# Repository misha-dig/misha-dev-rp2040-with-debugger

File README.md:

# misha-dev-rp2040-with-debugger
A compact-sized development board with two switchable debugger modes (BOOTSEL and SWD (debug/flash)) powered by a type-C receptacle connector.

# Description project
Single board with dual methods of uploading firmware into MCU RP2040 and not longer need to use Raspberry Pi debug probe, if use this board. 

# Requirement
Install and configure Raspberry Pi debug probe code, you can download from links https://github.com/raspberrypi/debugprobe
Will provided only board_pico_config.h in software directory. You will need to replace file from orginal file.

To install required lastest version of Raspberry Pi Pico SDK. Recommended version PICO SDK is above 2.0.0

# Testing SWD flashing and UART

Will provide binaries and instruction later.

# Technical specification
- Two RP2040 MCU (one for main functions of development board and one for debugger)
- USB Type-C connector receptacle (Best solution that not require to find uncommon USB cables)
- Normal input voltage from USB is 5.0 V, but absolute range is (4.5 - 5.5 VDC). This development board can power only USB cable as first prototyping. Unfortunately, don't allow to use external power source even 5V in current time. Use it is risk to damage your board. 
- Maximum output recommend current is 250mA for 3.3 voltage regulation, but 500mA is absolute maximum current in both output voltage 3.3V and 5.0V to avoid excessing heating voltage regulator due solder paste has melting point 138 C. 
- MCU clock 133 MHz
- RAM 264 kB.
- Flash memory size 16 - 128 Mbit, depending in your prototyping. Use Winbond flash memory series W25QxxxJVxxx as Raspberry Pi recommendation for RP2040 MCU. Required external flash memory each RP2040 in both MCUs. 

# Credit
* [Debugprobe](https://github.com/raspberrypi/debugprobe) (but I take portion source of code for only configuration of debugprobe due licensing complex and restriction of modification). I will planed to replace CMSIS-DAP software and hardware that support full open-source license and save BOM cost. Configuration CMSIS-DAP is licensed MIT, e.g. [board_pico_config.h](https://github.com/raspberrypi/debugprobe/blob/master/include/board_pico_config.h)

* [Raspberry Pi Documentation](https://www.raspberrypi.com/documentation/microcontrollers/) (Included: Hardware design with RP2040 and Getting started with RP2040)

* [Raspberry Pi Pico Datasheet](https://datasheets.raspberrypi.com/pico/pico-datasheet.pdf)

* [Getting started with Raspberry Pi
Pico-series](https://datasheets.raspberrypi.com/pico/getting-started-with-pico.pdf)

* [Raspberry Pi Licence Information](https://datasheets.raspberrypi.com/licence.html)

* [Licensing](https://www.raspberrypi.com/licensing/)

* [The design is based rp2040/Minimal-KiCAD.zip](https://datasheets.raspberrypi.com/rp2040/Minimal-KiCAD.zip) (Use downloaded circuits with mapping debugging and serial ports between two RP2040 MCUs)

* Thanks for developing excellent RP2040 MCU to Raspberry Pi that can develop software and hardware opensource!

# What I want to ask  

* Good luck with building your development board with debugger.
* I happy that help to solve problems

# Disclaimer and license

* PCB and sechmatics design are licensed licensed under CC BY-NC-ND 4.0. (C) Misha Zaslavskis

DESIGNS ARE PROVIDED “AS IS” AND THE AUTHOR DISCLAIMS ALL WARRANTIES WITH REGARD TO THESE DESIGNS INCLUDING ALL IMPLIED WARRANTIES OF MERCHANTABILITY AND FITNESS. IN NO EVENT SHALL THE AUTHOR BE LIABLE FOR ANY SPECIAL, DIRECT, INDIRECT, OR CONSEQUENTIAL DAMAGES OR ANY DAMAGES WHATSOEVER RESULTING FROM LOSS OF USE, DATA OR PROFITS, WHETHER IN AN ACTION OF CONTRACT, NEGLIGENCE OR OTHER TORTIOUS ACTION, ARISING OUT OF OR IN CONNECTION WITH THE USE OR PERFORMANCE OF THESE DESIGNS.

* Software (configuration of debugprobe) are licensed under MIT. (C) 2023 Raspberry Pi (Trading) Ltd.

THE SOFTWARE IS PROVIDED “AS IS”, WITHOUT WARRANTY OF ANY KIND, EXPRESS OR IMPLIED, INCLUDING BUT NOT LIMITED TO THE WARRANTIES OF MERCHANTABILITY, FITNESS FOR A PARTICULAR PURPOSE AND NONINFRINGEMENT. IN NO EVENT SHALL THE AUTHORS OR COPYRIGHT HOLDERS BE LIABLE FOR ANY CLAIM, DAMAGES OR OTHER LIABILITY, WHETHER IN AN ACTION OF CONTRACT, TORT OR OTHERWISE, ARISING FROM, OUT OF OR IN CONNECTION WITH THE SOFTWARE OR THE USE OR OTHER DEALINGS IN THE SOFTWARE.

* Software (testing API for this board) are licensed under BSD 3-Clause License. (C) Misha Zaslavskis

THIS SOFTWARE IS PROVIDED BY THE COPYRIGHT HOLDERS AND CONTRIBUTORS "AS IS"
AND ANY EXPRESS OR IMPLIED WARRANTIES, INCLUDING, BUT NOT LIMITED TO, THE
IMPLIED WARRANTIES OF MERCHANTABILITY AND FITNESS FOR A PARTICULAR PURPOSE ARE
DISCLAIMED. IN NO EVENT SHALL THE COPYRIGHT HOLDER OR CONTRIBUTORS BE LIABLE
FOR ANY DIRECT, INDIRECT, INCIDENTAL, SPECIAL, EXEMPLARY, OR CONSEQUENTIAL
DAMAGES (INCLUDING, BUT NOT LIMITED TO, PROCUREMENT OF SUBSTITUTE GOODS OR
SERVICES; LOSS OF USE, DATA, OR PROFITS; OR BUSINESS INTERRUPTION) HOWEVER
CAUSED AND ON ANY THEORY OF LIABILITY, WHETHER IN CONTRACT, STRICT LIABILITY,
OR TORT (INCLUDING NEGLIGENCE OR OTHERWISE) ARISING IN ANY WAY OUT OF THE USE
OF THIS SOFTWARE, EVEN IF ADVISED OF THE POSSIBILITY OF SUCH DAMAGE.

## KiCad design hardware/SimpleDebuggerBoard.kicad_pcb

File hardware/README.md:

## KiCAD Project Folder
This forder is contain KiCAD project files, so you can view/edit PCB and sechmatics by downloading this folder if neccesary.

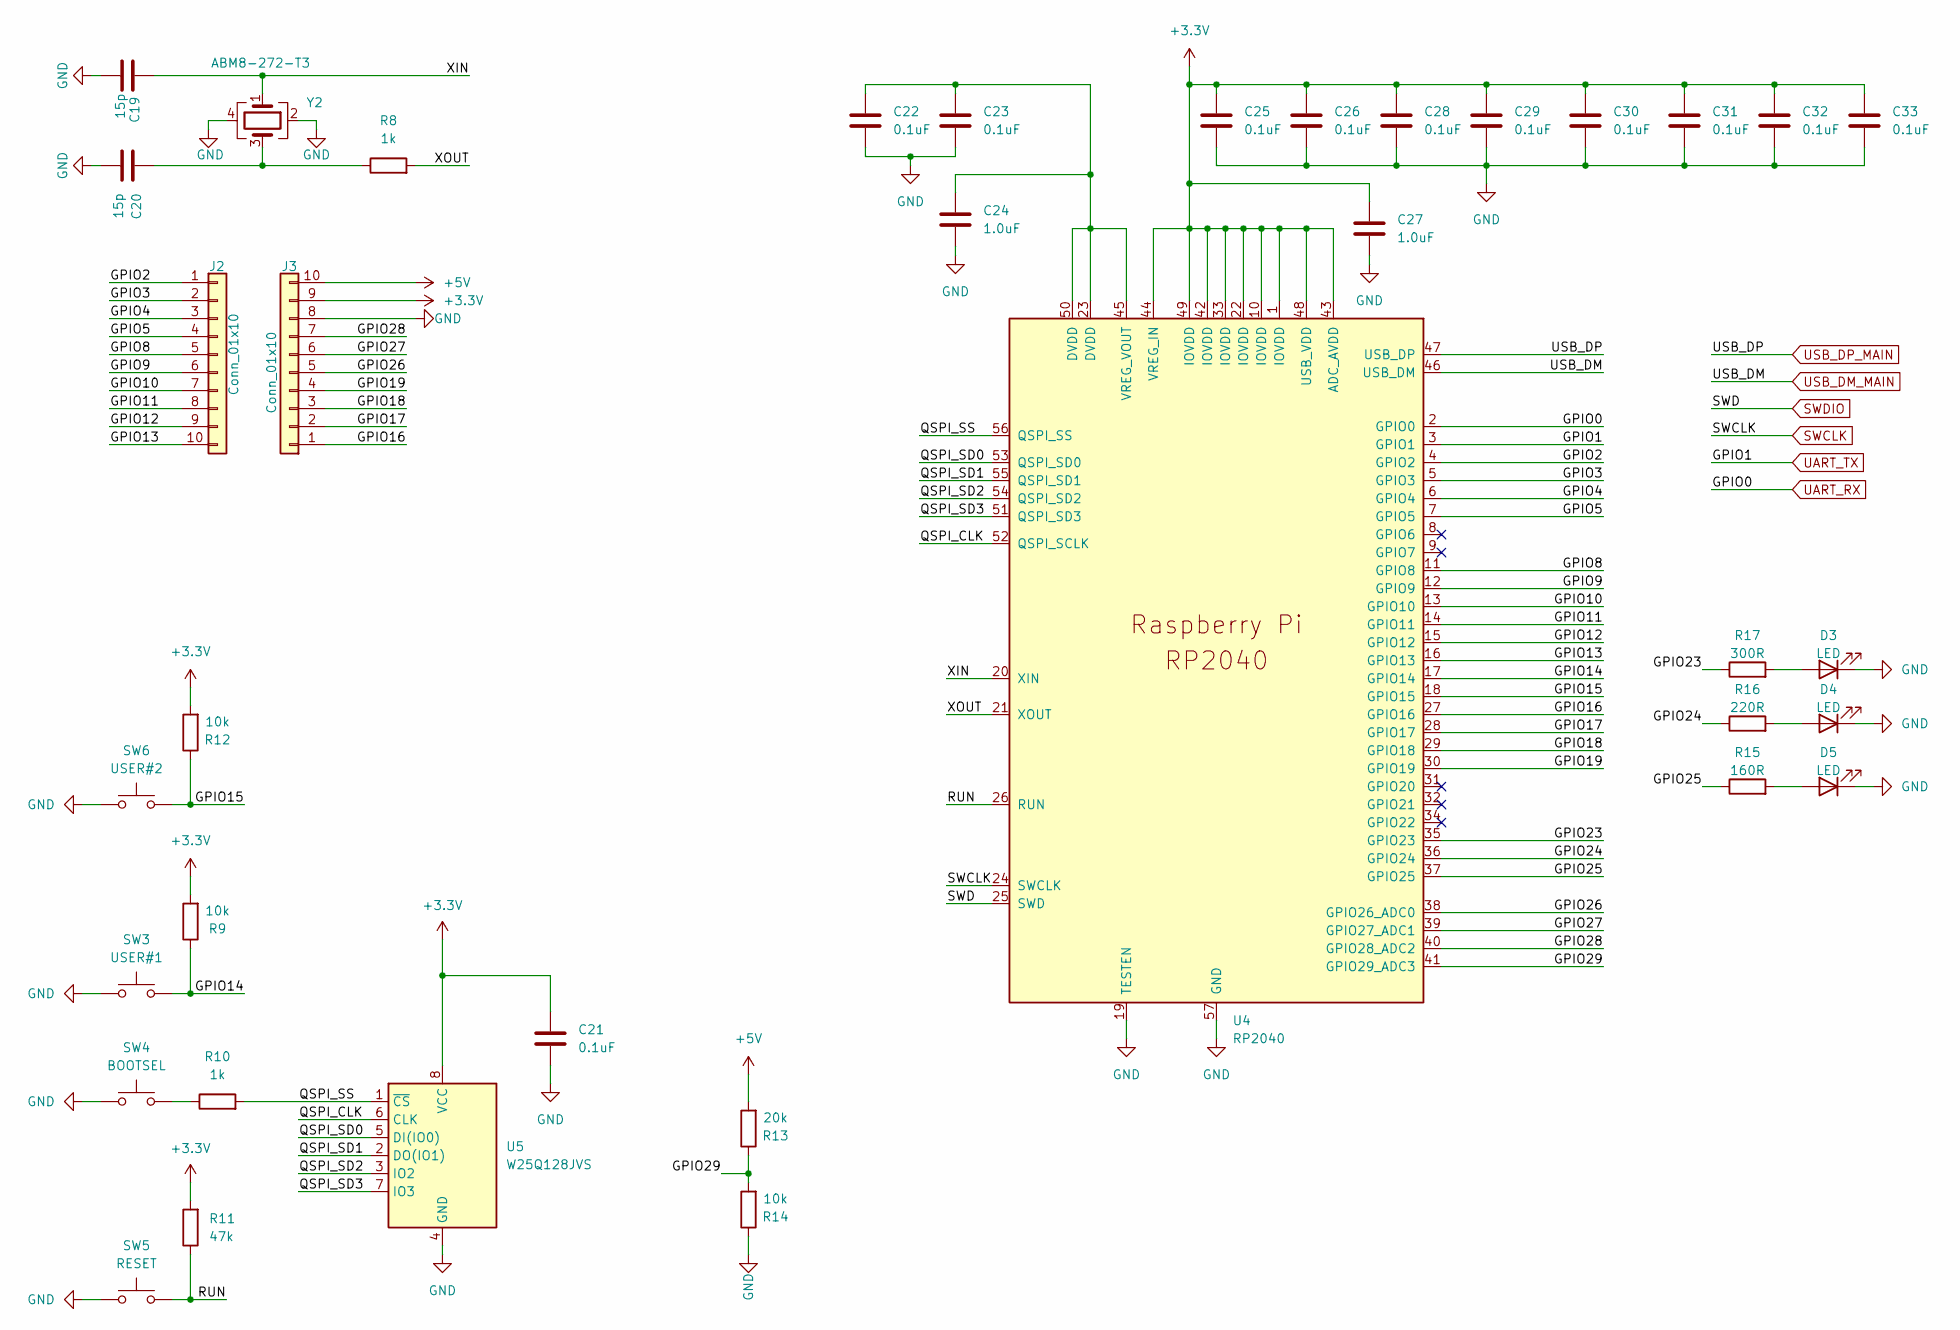
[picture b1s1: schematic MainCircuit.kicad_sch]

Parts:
C19, C20: 15p; C_0402_1005Metric_Pad0.74x0.62mm_HandSolder
C21, C22, C23, C25, C26, C28, C29, C30, C31, C32, C33: 0.1uF; C_0402_1005Metric_Pad0.74x0.62mm_HandSolder
C24, C27: 1.0uF; C_0603_1608Metric_Pad1.08x0.95mm_HandSolder
D3, D4, D5: LED; LED_0603_1608Metric
J2, J3: Conn_01x10; PinHeader_1x10_P2.54mm_Vertical
R8, R10: 1k; R_0402_1005Metric_Pad0.72x0.64mm
R9, R12, R14: 10k; R_0402_1005Metric_Pad0.72x0.64mm
R11: 47k; R_0402_1005Metric_Pad0.72x0.64mm
R13: 20k; R_0402_1005Metric_Pad0.72x0.64mm
R15: 160R; R_0402_1005Metric_Pad0.72x0.64mm
R16: 220R; R_0402_1005Metric_Pad0.72x0.64mm
R17: 300R; R_0402_1005Metric_Pad0.72x0.64mm
SW3: USER#1; SW_SPST_PTS810
SW4: BOOTSEL; SW_SPST_PTS810
SW5: RESET; SW_SPST_PTS810
SW6: USER#2; SW_SPST_PTS810
U4: RP2040; RP2040-QFN-56
U5: W25Q128JVS; SOIC-8_5.23x5.23mm_P1.27mm
Y2: ABM8-272-T3; Crystal_SMD_3225-4Pin_3.2x2.5mm

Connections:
+3.3V: C21.1, C25.1, C26.1, C27.1, C28.1, C29.1, C30.1, C31.1, C32.1, C33.1, J3.9, R9.2, R11.2, R12.2, U4.1 (IOVDD), U4.10 (IOVDD), U4.22 (IOVDD), U4.33 (IOVDD), U4.42 (IOVDD), U4.43 (ADC_AVDD), U4.44 (VREG_IN), U4.48 (USB_VDD), U4.49 (IOVDD), U5.8 (VCC); also elsewhere on the board
+5V: J3.10, R13.2; also elsewhere on the board
/MainCircuit/GPIO2: J2.1, U4.4 (GPIO2)
/MainCircuit/GPIO3: J2.2, U4.5 (GPIO3)
/MainCircuit/GPIO4: J2.3, U4.6 (GPIO4)
/MainCircuit/GPIO5: J2.4, U4.7 (GPIO5)
/MainCircuit/GPIO8: J2.5, U4.11 (GPIO8)
/MainCircuit/GPIO9: J2.6, U4.12 (GPIO9)
/MainCircuit/GPIO10: J2.7, U4.13 (GPIO10)
/MainCircuit/GPIO11: J2.8, U4.14 (GPIO11)
/MainCircuit/GPIO12: J2.9, U4.15 (GPIO12)
/MainCircuit/GPIO13: J2.10, U4.16 (GPIO13)
/MainCircuit/GPIO14: R9.1, SW3.1, U4.17 (GPIO14)
/MainCircuit/GPIO15: R12.1, SW6.1, U4.18 (GPIO15)
/MainCircuit/GPIO16: J3.1, U4.27 (GPIO16)
/MainCircuit/GPIO17: J3.2, U4.28 (GPIO17)
/MainCircuit/GPIO18: J3.3, U4.29 (GPIO18)
/MainCircuit/GPIO19: J3.4, U4.30 (GPIO19)
/MainCircuit/GPIO23: R17.1, U4.35 (GPIO23)
/MainCircuit/GPIO24: R16.1, U4.36 (GPIO24)
/MainCircuit/GPIO25: R15.1, U4.37 (GPIO25)
/MainCircuit/GPIO26: J3.5, U4.38 (GPIO26_ADC0)
/MainCircuit/GPIO27: J3.6, U4.39 (GPIO27_ADC1)
/MainCircuit/GPIO28: J3.7, U4.40 (GPIO28_ADC2)
/MainCircuit/GPIO29: R13.1, R14.2, U4.41 (GPIO29_ADC3)
/MainCircuit/QSPI_CLK: U4.52 (QSPI_SCLK), U5.6 (CLK)
/MainCircuit/QSPI_SD0: U4.53 (QSPI_SD0), U5.5 (DI(IO0))
/MainCircuit/QSPI_SD1: U4.55 (QSPI_SD1), U5.2 (DO(IO1))
/MainCircuit/QSPI_SD2: U4.54 (QSPI_SD2), U5.3 (IO2)
/MainCircuit/QSPI_SD3: U4.51 (QSPI_SD3), U5.7 (IO3)
/MainCircuit/QSPI_SS: R10.2, U4.56 (QSPI_SS), U5.1 (~CS)
/MainCircuit/RUN: R11.1, SW5.2, U4.26 (RUN)
/MainCircuit/XIN: C19.2, U4.20 (XIN), Y2.1
/MainCircuit/XOUT: R8.2, U4.21 (XOUT)
GND: C19.1, C20.1, C21.2, C22.2, C23.2, C24.2, C25.2, C26.2, C27.2, C28.2, C29.2, C30.2, C31.2, C32.2, C33.2, D3.1 (K), D4.1 (K), D5.1 (K), J3.8, R14.1, SW3.2, SW4.1, SW5.1, SW6.2, U4.19 (TESTEN), U4.57 (GND), U5.4 (GND), Y2.2, Y2.4; also elsewhere on the board
unnamed: C20.2, R8.1, Y2.3
unnamed: D3.2 (A), R17.2
unnamed: D4.2 (A), R16.2
unnamed: D5.2 (A), R15.2
unnamed: R10.1, SW4.2
unnamed: C22.1, C23.1, C24.1, U4.23 (DVDD), U4.45 (VREG_VOUT), U4.50 (DVDD)
SWCLK: U4.24 (SWCLK); also elsewhere on the board
SWDIO: U4.25 (SWD); also elsewhere on the board
UART_RX: U4.2 (GPIO0); also elsewhere on the board
UART_TX: U4.3 (GPIO1); also elsewhere on the board
USB_DM_MAIN: U4.46 (USB_DM); also elsewhere on the board
USB_DP_MAIN: U4.47 (USB_DP); also elsewhere on the board

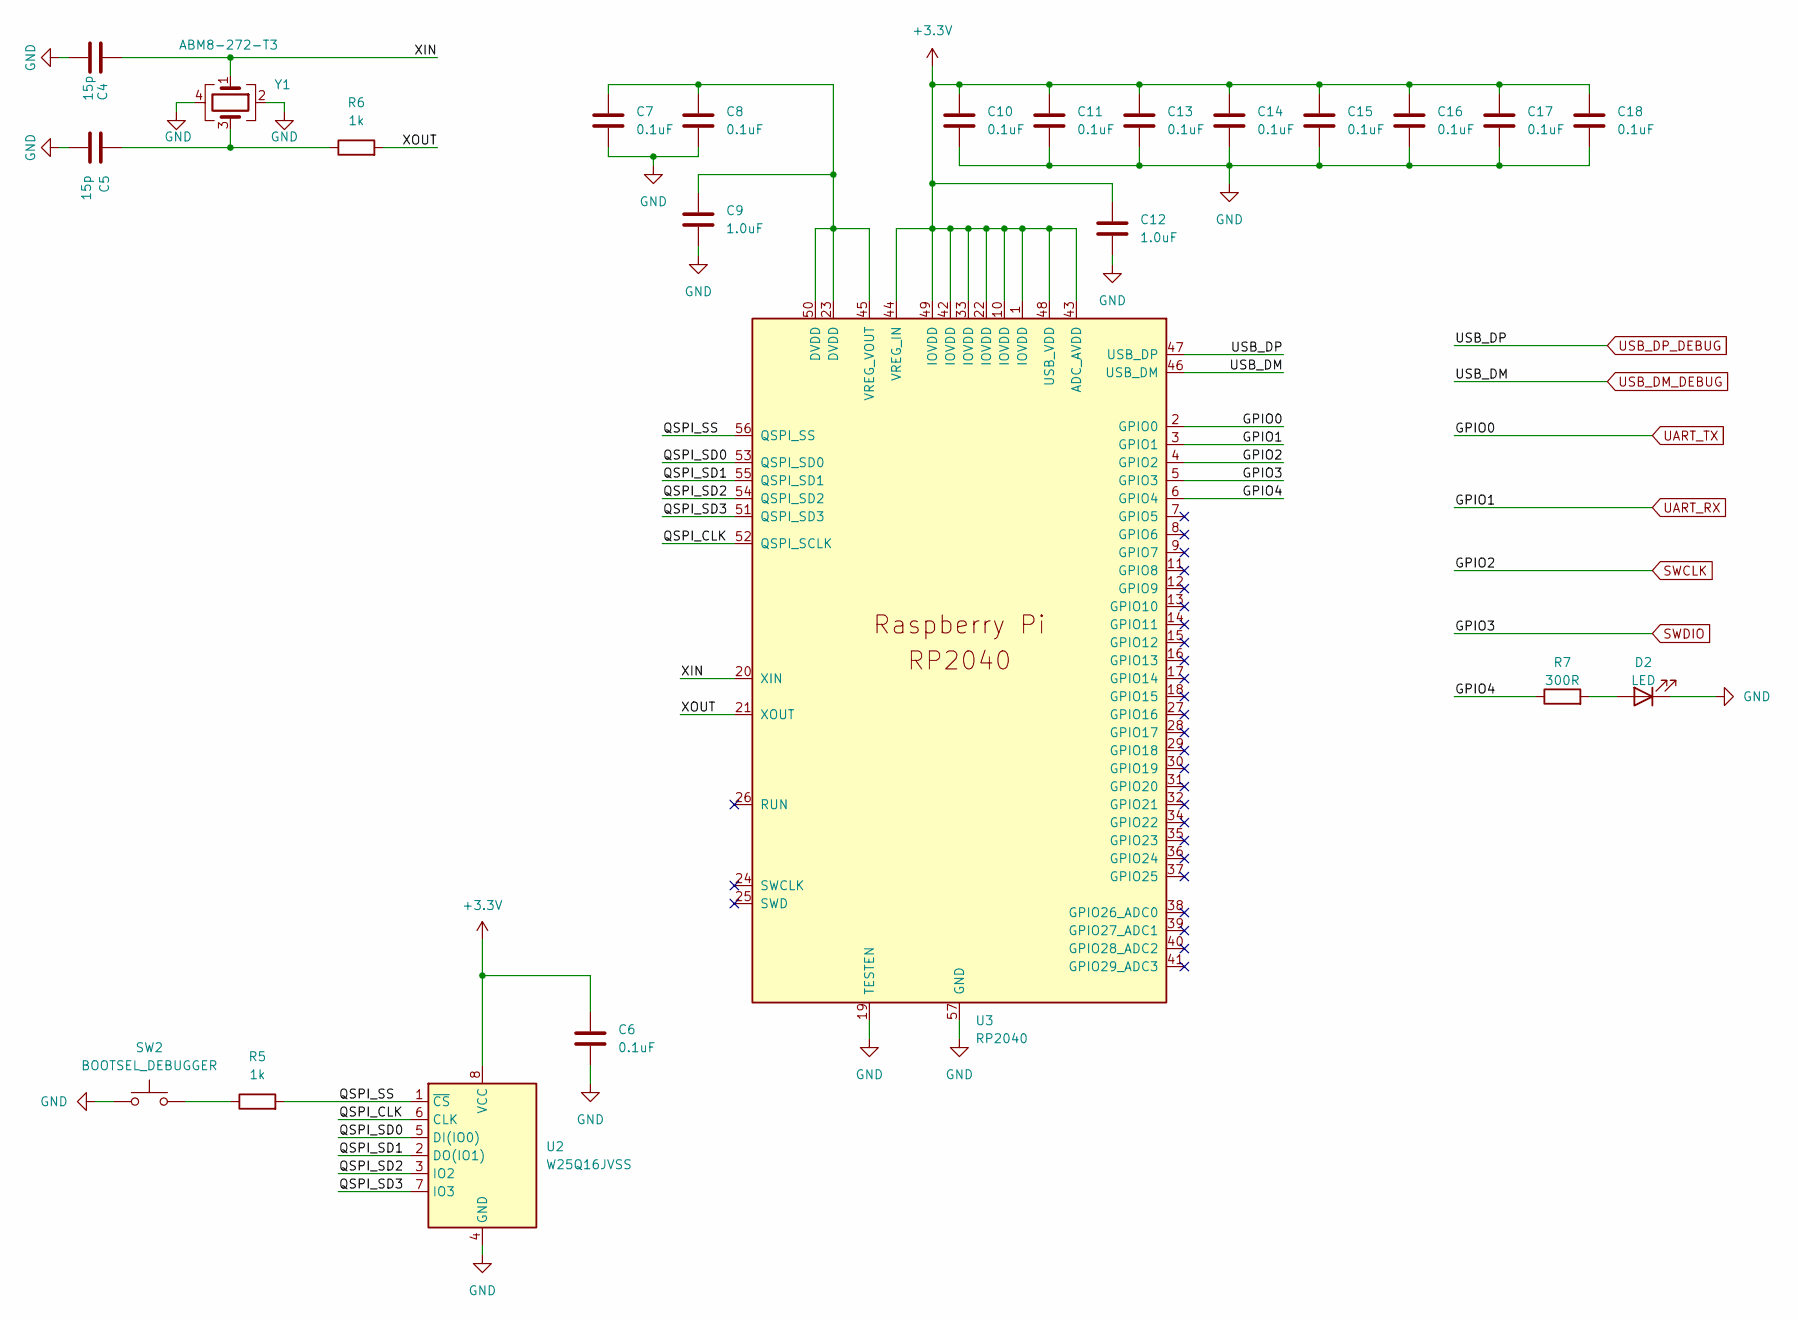
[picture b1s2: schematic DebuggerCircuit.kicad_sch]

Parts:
C4, C5: 15p; C_0402_1005Metric_Pad0.74x0.62mm_HandSolder
C6, C7, C8, C10, C11, C13, C14, C15, C16, C17, C18: 0.1uF; C_0402_1005Metric_Pad0.74x0.62mm_HandSolder
C9, C12: 1.0uF; C_0603_1608Metric_Pad1.08x0.95mm_HandSolder
D2: LED; LED_0603_1608Metric
R5, R6: 1k; R_0402_1005Metric_Pad0.72x0.64mm
R7: 300R; R_0402_1005Metric_Pad0.72x0.64mm
SW2: BOOTSEL_DEBUGGER; SW_SPST_PTS810
U2: W25Q16JVSS; SOIC-8_5.23x5.23mm_P1.27mm
U3: RP2040; RP2040-QFN-56
Y1: ABM8-272-T3; Crystal_SMD_3225-4Pin_3.2x2.5mm

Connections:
+3.3V: C6.1, C10.1, C11.1, C12.1, C13.1, C14.1, C15.1, C16.1, C17.1, C18.1, U2.8 (VCC), U3.1 (IOVDD), U3.10 (IOVDD), U3.22 (IOVDD), U3.33 (IOVDD), U3.42 (IOVDD), U3.43 (ADC_AVDD), U3.44 (VREG_IN), U3.48 (USB_VDD), U3.49 (IOVDD); also elsewhere on the board
/DebuggerCircuit/GPIO4: R7.1, U3.6 (GPIO4)
/DebuggerCircuit/QSPI_CLK: U2.6 (CLK), U3.52 (QSPI_SCLK)
/DebuggerCircuit/QSPI_SD0: U2.5 (DI(IO0)), U3.53 (QSPI_SD0)
/DebuggerCircuit/QSPI_SD1: U2.2 (DO(IO1)), U3.55 (QSPI_SD1)
/DebuggerCircuit/QSPI_SD2: U2.3 (IO2), U3.54 (QSPI_SD2)
/DebuggerCircuit/QSPI_SD3: U2.7 (IO3), U3.51 (QSPI_SD3)
/DebuggerCircuit/QSPI_SS: R5.2, U2.1 (~CS), U3.56 (QSPI_SS)
/DebuggerCircuit/XIN: C4.2, U3.20 (XIN), Y1.1
/DebuggerCircuit/XOUT: R6.2, U3.21 (XOUT)
GND: C4.1, C5.1, C6.2, C7.2, C8.2, C9.2, C10.2, C11.2, C12.2, C13.2, C14.2, C15.2, C16.2, C17.2, C18.2, D2.1 (K), SW2.1, U2.4 (GND), U3.19 (TESTEN), U3.57 (GND), Y1.2, Y1.4; also elsewhere on the board
unnamed: C5.2, R6.1, Y1.3
unnamed: D2.2 (A), R7.2
unnamed: R5.1, SW2.2
unnamed: C7.1, C8.1, C9.1, U3.23 (DVDD), U3.45 (VREG_VOUT), U3.50 (DVDD)
SWCLK: U3.4 (GPIO2); also elsewhere on the board
SWDIO: U3.5 (GPIO3); also elsewhere on the board
UART_RX: U3.3 (GPIO1); also elsewhere on the board
UART_TX: U3.2 (GPIO0); also elsewhere on the board
USB_DM_DEBUG: U3.46 (USB_DM); also elsewhere on the board
USB_DP_DEBUG: U3.47 (USB_DP); also elsewhere on the board

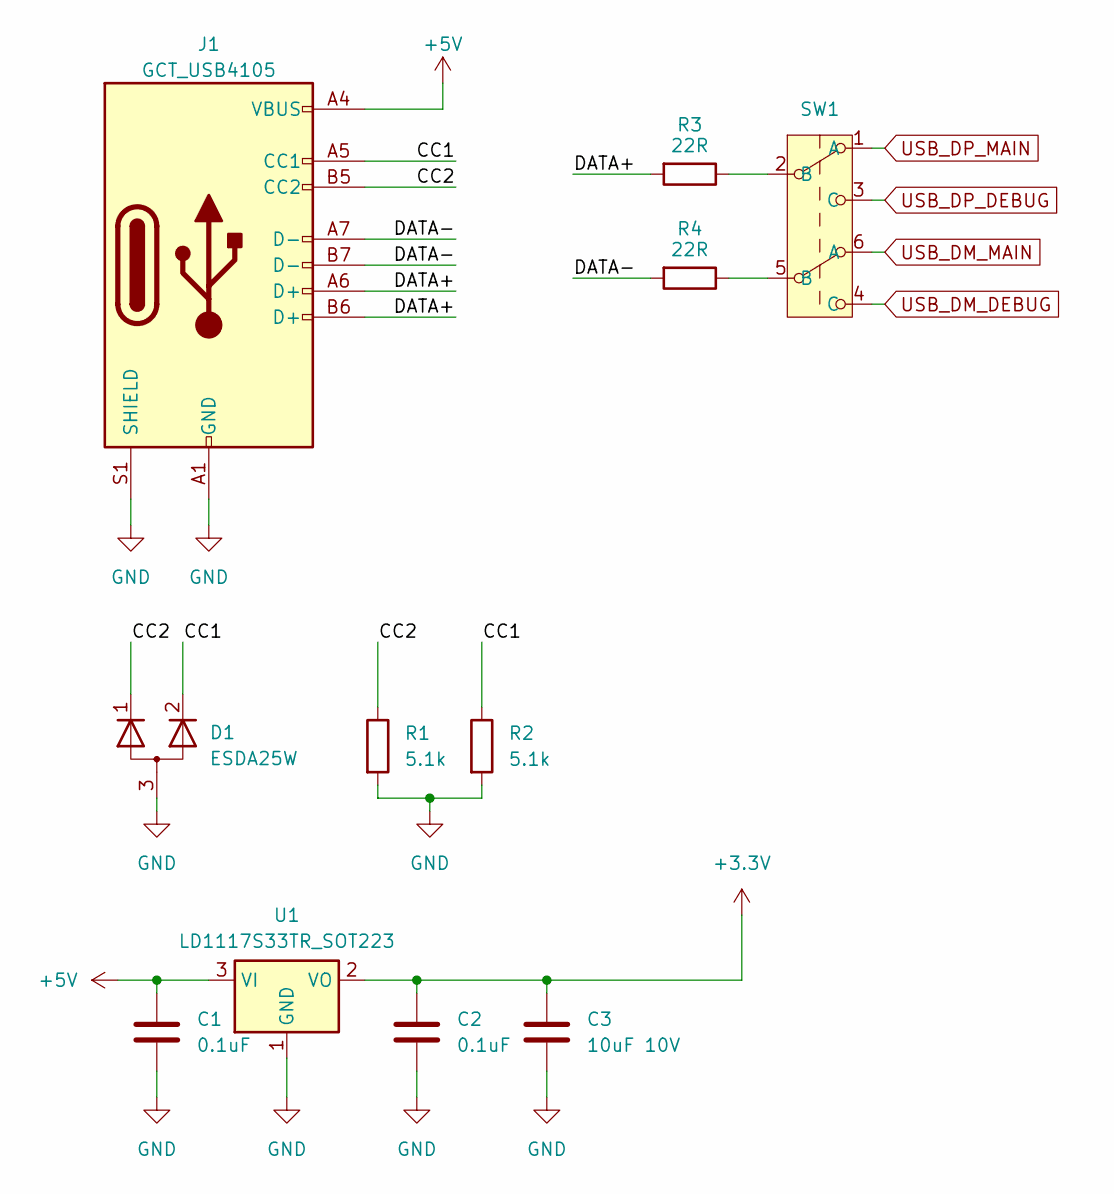
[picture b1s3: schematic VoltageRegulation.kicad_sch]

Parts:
C1, C2: 0.1uF; C_0402_1005Metric_Pad0.74x0.62mm_HandSolder
C3: 10uF 10V; C_1206_3216Metric_Pad1.33x1.80mm_HandSolder
D1: ESDA25W; SOT-323_SC-70
J1: GCT_USB4105; USB_C_Receptacle_GCT_USB4105-xx-A_16P_TopMnt_Horizontal
R1, R2: 5.1k; R_0402_1005Metric_Pad0.72x0.64mm
R3, R4: 22R; R_0402_1005Metric_Pad0.72x0.64mm_HandSolder
SW1: MST22D18G2-125-footprint
U1: LD1117S33TR_SOT223; SOT-223-3_TabPin2

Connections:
+3.3V: C2.1, C3.1, U1.2 (VO); also elsewhere on the board
+5V: C1.1, J1.A4 (VBUS), J1.A9 (VBUS), J1.B4 (VBUS), J1.B9 (VBUS), U1.3 (VI); also elsewhere on the board
/VoltageRegulation/CC1: D1.2 (K), J1.A5 (CC1), R2.1
/VoltageRegulation/CC2: D1.1 (K), J1.B5 (CC2), R1.1
/VoltageRegulation/DATA+: J1.A6 (D+), J1.B6 (D+), R3.2
/VoltageRegulation/DATA-: J1.A7 (D-), J1.B7 (D-), R4.2
GND: C1.2, C2.2, C3.2, D1.3 (A), J1.A1 (GND), J1.A12 (GND), J1.B1 (GND), J1.B12 (GND), J1.S1 (SHIELD), R1.2, R2.2, U1.1 (GND); also elsewhere on the board
unnamed: R3.1, SW1.2 (B)
unnamed: R4.1, SW1.5 (B)
USB_DM_DEBUG: SW1.4 (C); also elsewhere on the board
USB_DM_MAIN: SW1.6 (A); also elsewhere on the board
USB_DP_DEBUG: SW1.3 (C); also elsewhere on the board
USB_DP_MAIN: SW1.1 (A); also elsewhere on the board

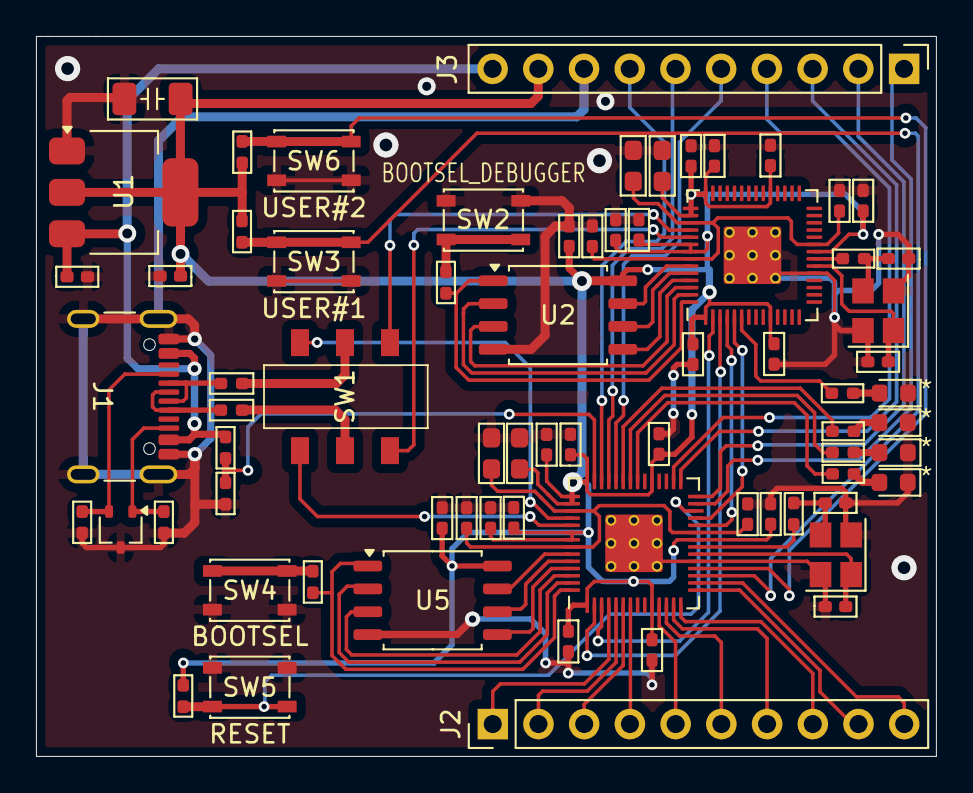
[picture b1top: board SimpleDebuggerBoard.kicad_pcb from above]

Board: 2 copper layers, 50.0 x 40.0 mm, 71 parts (0 on the bottom side), 68 nets.

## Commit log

2024-11-02 Update README.md
    Add description, instructions
2024-11-02 Add files via upload
    Added KICAD project files, included not limit to Sechmatics, PCBs, Libraries
2024-11-15 Update README.md
    Update and adding extra information about licenses
    Added credits that I adapted in this project
2024-11-15 Update README.md
    Correct links
2024-11-15 Rename software/board_pico_config.h to software/config_debugprobe/board_pico_config.h
    Make software organization with separated between debug probe and testing software codes
2024-11-15 Update README.md
    Added Raspberry license files as reference
2024-11-20 Update README.md
    Add detailed licensing about software and hardware. Make argument of why I can take portion of software debug probe (e.g. taking configuration code)
2024-11-20 Update README.md
    Make clarification about software licensing
2024-11-20 Update board_pico_config.h
    Update license statement. BSD license was made mistake. Using original license statement with stated modification.
